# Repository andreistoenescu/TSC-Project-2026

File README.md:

# Watch_TSC_Project

Un smartwatch construit de la zero — schematic, PCB 4 straturi, carcasă 3D — centrat pe nRF52840 și un display E-Paper care nu consumă energie când nu se schimbă nimic pe ecran.

---

## Ce este acest proiect

Scopul a fost să proiectez un ceas inteligent complet: de la primul simbol în schematic până la modelul 3D gata de imprimat. Nu un modul dev board montat într-o carcasă, ci un PCB custom cu toate componentele alese și integrate manual.

Tehnologia cheie este display-ul **E-Paper (e-ink)** — odată ce afișează ceva, menține imaginea fără niciun consum de curent. Combinat cu modurile deep sleep ale nRF52840 (1.5μA), rezultatul este un dispozitiv care poate rula zile întregi dintr-o celulă LiPo mică.

### Ce integrează placa

| Subsistem | Componentă | Rol |
|-----------|-----------|-----|
| Microcontroller | nRF52840 | Cortex-M4 64MHz, BT 5.0, USB nativ |
| Display | E-Paper via SPI | Afișaj zero-consum în standby |
| Mișcare | BMA423 | Accelerometru 3 axe, step counter, wake-on-wrist |
| Încărcare | BQ25180 | LiPo charger programabil I2C, 5mA–1A |
| Alimentare | RT6160 | Buck-Boost 3.3V stabil indiferent de tensiunea bateriei |
| Baterie | MAX17048 | Fuel gauge ModelGauge, fără shunt rezistor |
| Feedback | DRV2605 | Driver haptic, 123 efecte ERM/LRA |
| USB | KH-TYPE-C-16P + USBLC6 | Conector C16P cu protecție ESD ±15kV |
| Input | EVP-AKE31A ×3 | Butoane tactile SMD ultra-subțiri |
| RF | 2450AT18B100E | Antenă SMD 2.45GHz pentru Bluetooth |

---

## Diagrama bloc a sistemului

```
  USB-C (5V)
      │
      ▼
 ┌─────────┐    VBUS      ┌──────────────┐
 │  ESD    │─────────────▶│  BQ25180     │ LiPo Charger
 │USBLC6   │              │  (I2C 0x6A)  │◀─── Baterie LiPo
 └────┬────┘              └──────┬───────┘
      │ D+/D−                    │ VBAT
      │                          ▼
      │                   ┌──────────────┐
      │                   │  MAX17048    │ Fuel Gauge
      │                   │  (I2C 0x36)  │
      │                   └──────┬───────┘
      │                          │ VBAT
      │                          ▼
      │                   ┌──────────────┐
      │                   │   RT6160     │ Buck-Boost DC/DC
      │                   │  (I2C 0x62)  │─── 3V3 ───────────┐
      │                   └──────────────┘                    │
      │                                                       │
      └───────────────────────────────────────────────────────▼
                                                     ┌─────────────────┐
                    ┌── SPI ──▶ E-Paper Display       │                 │
                    │                                 │   nRF52840      │
                    ├── I2C ──▶ BMA423  (0x18)        │   Cortex-M4     │
                    │       ──▶ DRV2605 (0x5A)        │   64MHz / BT5.0 │
                    │       ──▶ BQ25180 (0x6A)        │                 │
                    │       ──▶ RT6160  (0x62)        └────────┬────────┘
                    │       ──▶ MAX17048(0x36)                 │
                    │                                          │ GPIO
                    ├── SWD ──▶ TC2030-IDC                     │
                    │                                          ▼
                    └── USB ──▶ (intern nRF52840)      Butoane ×3 / IMU INT / HAPTIC_EN
```

---

## Componente — BOM complet

| Ref | Part Number | Descriere | Qty |
|-----|------------|-----------|:---:|
| U1 | nRF52840-QIAA | MCU ARM Cortex-M4, BT 5.0, USB 2.0, 1MB Flash | 1 |
| IC1 | BQ25180YBGR | LiPo charger liniar 1A I2C, 8-DSBGA | 1 |
| IC2 | DRV2605YZFR | Haptic driver ERM/LRA I2C 123 efecte, 9-BGA | 1 |
| IC3 | BMA423 | Accelerometru MEMS triaxial 12-bit, LGA-12 | 1 |
| U3 | MAX17048G+T10 | Fuel gauge ModelGauge 1-cell, SOT-23-6 | 1 |
| IC9 | RT6160AWSC | Buck-Boost DC/DC 800mA I2C, 15-WL-CSP | 1 |
| D3 | USBLC6-2SC6Y | TVS ESD ±15kV bidirecțional USB, SOT-23-6 | 1 |
| J4 | KH-TYPE-C-16P | Conector USB-C 16 pini SMD | 1 |
| J1 | 503480-2400 | Conector FPC/FFC 0.5mm pas 24 circuite | 1 |
| J2 | TC2030-IDC | Tag-Connect SWD 6 pini footprint-only | 1 |
| Q2 | DMG2305UX-7 | P-MOSFET 20V/4.2A, SOT-23 | 1 |
| Q3 | SI1308EDL-T1-GE3 | N-MOSFET 30V/1.5A, SC-70 | 1 |
| D1,D2,D5 | MBR0530 | Schottky 30V/500mA, SOD-123 | 3 |
| SW_* | EVP-AKE31A | Buton tactil SMD ultra-subțire Panasonic | 3 |
| ANT1 | 2450AT18B100E | Antenă SMD 2.45GHz Johanson | 1 |
| L7 | FTC252012SR47MBCA | Inductor 0.47μH SMD 2016 | 1 |
| L5 | 744043680 | Inductor 68μH WE-TPC SMD | 1 |
| X1 | Crystal 32MHz | Oscilator SMD 32MHz 2016 | 1 |
| X2 | Crystal 32.768kHz | Oscilator RTC 32.768kHz 3215 SMD | 1 |
| Cx | — | Condensatoare SMD 0201/0402, 1pF–22μF | ~50 |
| Rx | — | Rezistoare SMD 0201, 2.2Ω–10kΩ | ~15 |
| Lx | — | Inductoare SMD 0402, 3.9nH–10μH | ~4 |
| TP_* | TP20R | Test pad SMD 2mm | 14 |
| SJ1 | — | Solder jumper SMD | 1 |

---

## Hardware în detaliu

### Cum circulă energia

Bateria LiPo (3.7–4.2V) alimentează regulatorul **RT6160** care produce un 3V3 stabil pentru toată placa. Când e conectat USB-C, VBUS (5V) merge direct la **BQ25180** care preia încărcarea bateriei independent de restul sistemului. nRF52840 monitorizează ambele stări: știe când USB e prezent (CHARGER_PG) și câtă baterie a mai rămas (MAX17048 via I2C).

Componentele cu consum ridicat — display-ul și haptic driver-ul — sunt controlate prin MOSFET-uri (Q2/Q3), astfel că nRF52840 le poate tăia complet alimentarea când nu sunt necesare.

### Magistrala I2C — 5 periferice pe aceleași fire

| Componentă | Adresă I2C | Ce face |
|------------|:----------:|---------|
| BQ25180 | 0x6A | Controlează curentul și tensiunea de încărcare |
| RT6160 | 0x62 | Ajustează tensiunea de ieșire dacă e necesar |
| BMA423 | 0x18 | Livrează date accelerometru, numără pași |
| MAX17048 | 0x36 | Raportează SOC% și tensiunea celulei |
| DRV2605 | 0x5A | Selectează și redă efecte tactile |

Clock pe **P0.06**, date pe **P0.07**. Rezistoare de pull-up pe ambele linii.

### SPI — display E-Paper

Comunicație write-only spre display (nu există linie MISO — displayul nu trimite date înapoi). Frecvență maximă 4MHz. Pe lângă SCK și MOSI, display-ul are nevoie de 3 semnale GPIO suplimentare: DC (Data/Command), RST (reset hardware) și BUSY (ceasul trebuie să aștepte când displayul procesează un refresh).

### SWD — programare și debug

Conectorul **TC2030-IDC** (Tag-Connect, fără pini fizici pe PCB) expune SWDIO, SWDCLK, SWO și RESET. Nu ocupă spațiu vertical în ansamblu — cablul de programare se atașează temporar prin spring pins direct pe pad-urile de pe PCB.

### Bluetooth și antena

Antena **2450AT18B100E** este o antenă SMD ceramică pentru 2.4GHz, plasată în colțul plăcii cu un cutout în substrat sub ea. Cutout-ul elimină FR4-ul (material dielelectric cu pierderi la 2.4GHz) din zona de radiație, îmbunătățind câștigul și SWR-ul antenei. Cristalul de 32MHz asigură referința de frecvență pentru radio.

### Cristalul de 32.768kHz — RTC în sleep

Al doilea oscilator, la 32.768kHz, alimentează timer-ul RTC al nRF52840 și rămâne activ chiar și în deep sleep. Permite ceasului să știe ora exactă și să se trezească la intervale precise fără să țină procesorul pornit.

### BMA423 — mai mult decât un accelerometru

BMA423 are un procesor intern dedicat care rulează algoritmii de step counting și wake-on-wrist fără să implice nRF52840. Când detectează mișcarea caracteristică ridicării mâinii, trimite o întrerupere pe **P1.08 (IMU_INT1)** care trezește MCU-ul din deep sleep în microsecunde. Consum în această stare: **0.9μA**.

### Estimare consum și autonomie

| Scenariu | Curent estimat |
|----------|:-------------:|
| nRF52840 TX Bluetooth activ | 6.26 mA |
| nRF52840 RX Bluetooth activ | 4.82 mA |
| Refresh display E-Paper | ~26 mA (câteva secunde) |
| BMA423 monitorizare continuă | 130 μA |
| MAX17048 fuel gauge activ | 23 μA |
| DRV2605 vibrație activă | 5 mA |
| nRF52840 deep sleep + RTC + BMA low-power | ~50–100 μA |

**Consum mediu în utilizare normală** (BT conectat periodic, display refresh la fiecare minut, IMU activ): **6–8 mA** la 3.3V.

Cu o baterie LiPo de **300mAh**: autonomie estimată **35–50 ore**.

---

## Alocarea pinilor nRF52840

### Display E-Paper (SPI)

| Pin MCU | Semnal | Direcție | Descriere |
|---------|--------|:--------:|-----------|
| P0.02 / AIN0 | SCK | OUT | Clock SPI pentru display |
| P0.03 / AIN1 | MOSI | OUT | Date seriale spre display |
| P0.05 / AIN3 | EPD_CS | OUT | Chip select, activ LOW |
| P0.15 | EPD_RST | OUT | Reset hardware display, activ LOW |
| P0.16 | EPD_DC | OUT | LOW = comandă, HIGH = date |
| P0.17 | EPD_BUSY | IN | HIGH când displayul procesează |

### Periferice I2C

| Pin MCU | Semnal | Descriere |
|---------|--------|-----------|
| P0.06 | SCL | Clock comun pentru toate perifericele I2C |
| P0.07 | SDA | Date bidirecționale I2C |
| P0.08 | IMU_INT2 | Întrerupere secundară BMA423 (step counter) |
| P1.08 | IMU_INT1 | Întrerupere primară BMA423 (wake-on-wrist) |
| P0.10 / NFC2 | FUELGAUGE_ALT | Alarmă MAX17048 la baterie scăzută |
| P0.11 | CHARGER_PG | Power Good BQ25180 — 1 când USB e valid |
| P0.12 | HAPTIC_EN | Enable DRV2605, activ HIGH |

### Butoane și control

| Pin MCU | Semnal | Descriere |
|---------|--------|-----------|
| P0.13 | BTN_UP | Buton sus (navigare meniu) |
| P0.14 | BTN_ENT | Buton enter / confirmare |
| P1.02 | BTN_DN | Buton jos (navigare meniu) |

### USB, SWD și ceasuri

| Pin MCU | Semnal | Interfață | Descriere |
|---------|--------|:---------:|-----------|
| D+ | USB_DP | USB | Linie diferențială pozitivă, prin ESD |
| D− | USB_DM | USB | Linie diferențială negativă, prin ESD |
| VBUS | 5V_USB | PWR | Detecție USB prezent → BQ25180 |
| SWDIO | SWDIO | SWD | Date programare/debug |
| SWDCLK | SWDCLK | SWD | Clock programare/debug |
| SWO | SWO | SWD | Serial Wire Output (trace) |
| P0.18 / RESET | RESET | GPIO | Reset hardware MCU |
| ANT | RF | RF | Antenă Bluetooth 2.4GHz |
| XC1, XC2 | XTAL_32M | CLK | Cristal 32MHz — clock principal |
| XL1, XL2 | XTAL_32K | CLK | Cristal 32.768kHz — RTC sleep |

---

## PCB — decizii de proiectare

### 4 straturi: de ce și cum

| Strat | Conținut |
|-------|---------|
| **L1 — Top** | Toate componentele SMD + rutare semnale principale |
| **L2** | Plan de masă GND continuu |
| **L3** | Plan de alimentare 3V3 |
| **L4 — Bottom** | Rutare secundară + via connections |

Planul de masă pe L2 direct sub stratul de semnal L1 minimizează inductanța buclei de return pentru fiecare traseu. Fără acest plan, semnalele SPI și I2C ar genera mai mult EMI și ar fi mai sensibile la zgomot. Planul de 3V3 pe L3 reduce impedanța de alimentare, esențial pentru vârfurile de curent ale nRF52840 în TX.

### Via-in-pad

BQ25180, RT6160, DRV2605 și MAX17048 vin în packaging BGA/CSP cu pitch sub 0.5mm — imposibil de rutat cu via-uri laterale în spațiul disponibil. Soluția: via-uri plasate direct în centrul pad-urilor BGA. Acestea trebuie **umplute cu rășină epoxidică și planarize** (filled & capped) înainte de HASL/ENIG, altfel pasta de lipit curge în via și jointul devine defectuos.

### Cutout sub antenă

Substatul FR4 este un material cu pierderi dielectrice la 2.4GHz. Lăsat sub zona de radiație a antenei 2450AT18B100E, absoarbe o parte din energia RF și detune antena față de 50Ω. Soluția: un decupaj fizic al PCB-ului sub jumătatea neconectată a antenei, astfel că aceasta radiază în aer.

### 14 test pad-uri TP20R

Distribuite pe semnalele: 3V3, VBAT, GND, SDA, SCL, SWDCLK, SWDIO, SWO, RESET, VREG. Permit conectarea unui multimetru sau logicanalyzer după asamblare fără a fi nevoie de probe pe QFN/BGA.

---

## Ansamblu 3D

Modelat complet în **Autodesk Fusion 360**. Ansamblul verifică că totul se potrivește fizic înainte de fabricație.

Stratificarea de jos în sus:

```
  ┌─────────────────────────┐  ← Cadru superior + geam display
  │     Display E-Paper     │  ← Panou e-ink + cablu FPC
  │         PCB             │  ← Placa cu toate componentele
  │      Baterie LiPo       │  ← Celulă cu fire sudate pe test pads
  └─────────────────────────┘  ← Carcasă inferioară
```

Butoanele (×3) sunt accesibile prin locașuri în carcasa inferioară, pe laterale. Conectorul USB-C iese prin fanta frontală a carcasei. Shaker-ul haptic este montat cilindric în spațiul rămas lângă baterie.

---

## Galerie

### PCB — Layout 2D

### PCB — Randare 3D

### Ceas asamblat

### Exploded View

### Baterie LiPo

### Display E-Paper

### Motor Haptic

---

## Structura repository-ului

```
Watch_TSC_Project/
│
├── Hardware/
│   ├── PCB_2D.brd              # Fișier board KiCad/Eagle
│   ├── Schematic_final.sch     # Schematic complet
│   └── Schematic_final.pdf     # Export PDF schematic
│
├── Manufacturing/
│   ├── gerbers.zip             # Fișiere Gerber pentru fabricație PCB
│   ├── Watch_TSC_bom.bom       # Bill of Materials pentru comandă componente
│   ├── PnP_Watch_TSC_front.cpl # Pick & Place față
│   └── PnP_Watch_TSC_back.cpl  # Pick & Place spate
│
├── Mechanical/
│   ├── Exploded_Watch_3D.zip   # Export STEP ansamblu exploded
│   └── Watch_3D.f3z            # Proiect Autodesk Fusion 360
│
├── Images/                     # Randări și capturi PCB
│
├── LICENSE
└── README.md
```

---

MIT License — Copyright 2026 Stoenescu Constantin-Andrei

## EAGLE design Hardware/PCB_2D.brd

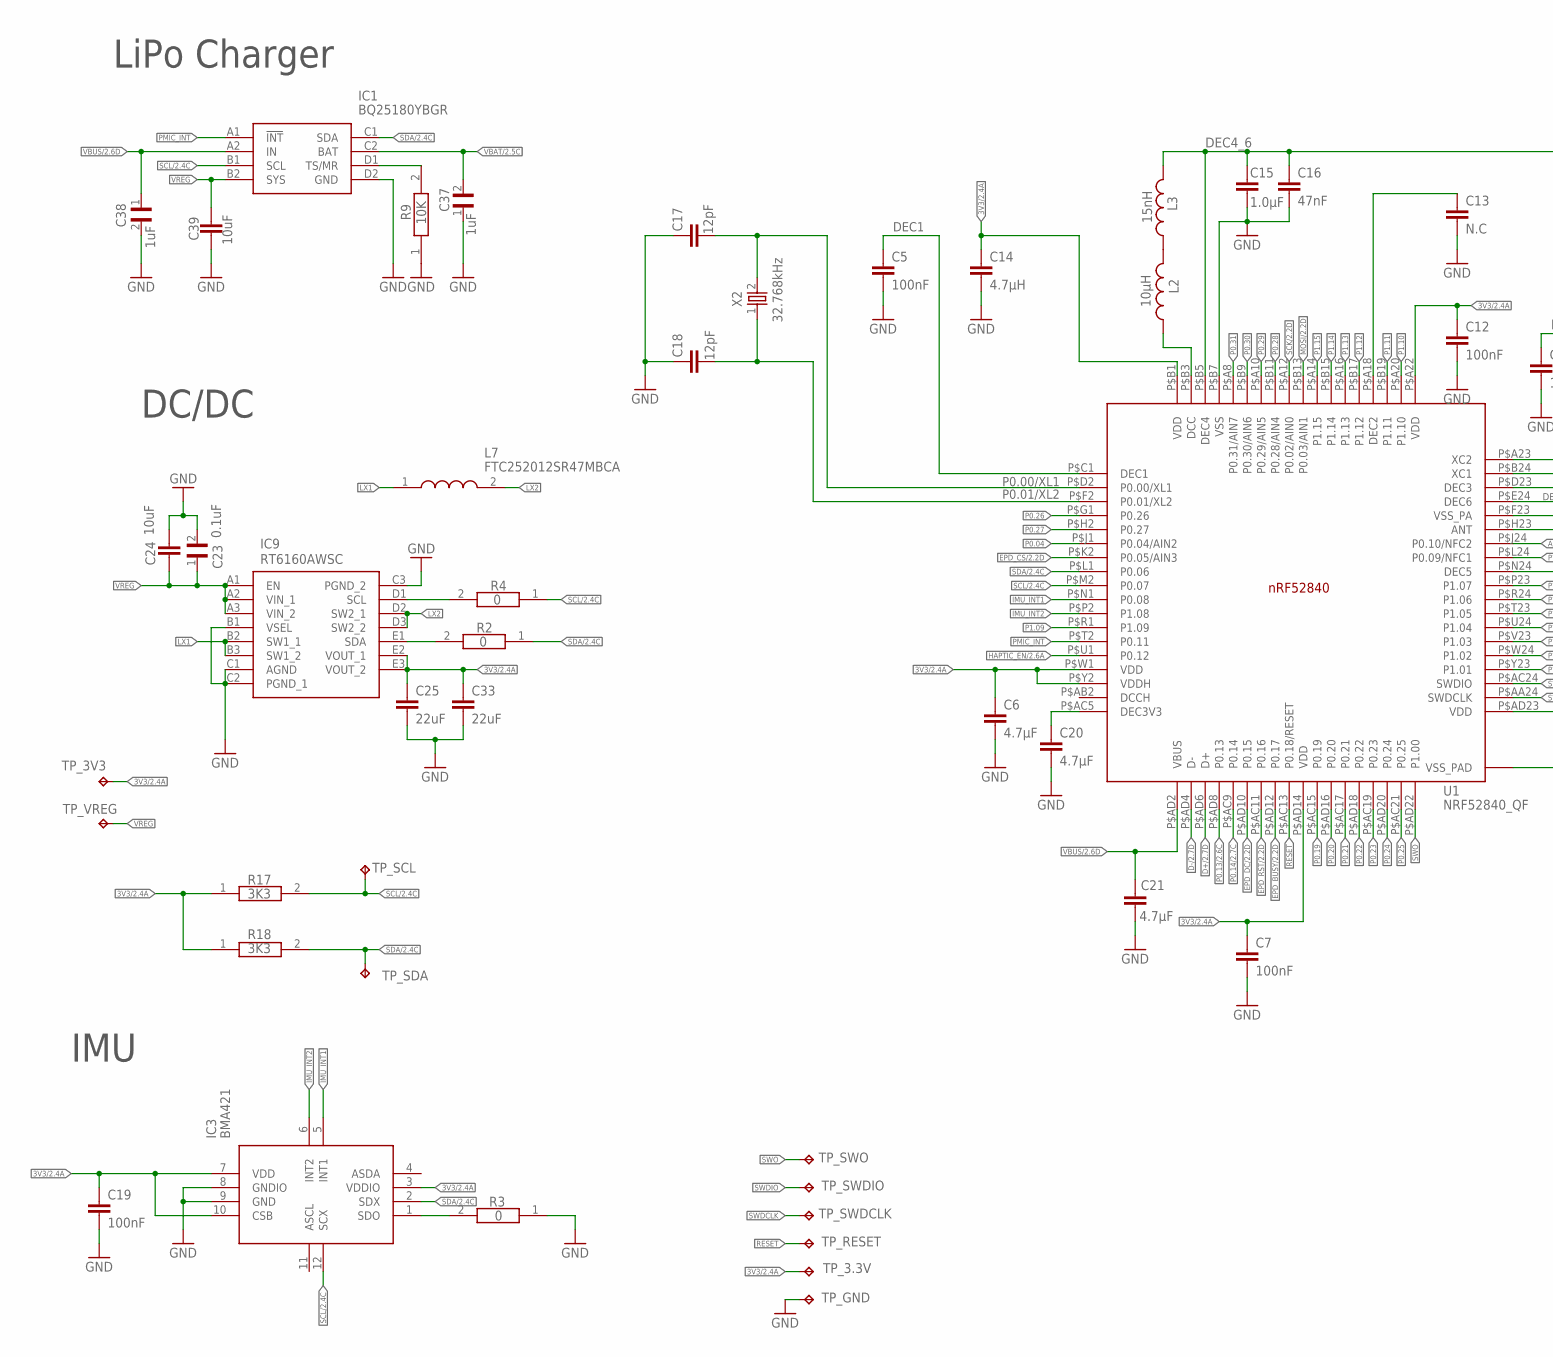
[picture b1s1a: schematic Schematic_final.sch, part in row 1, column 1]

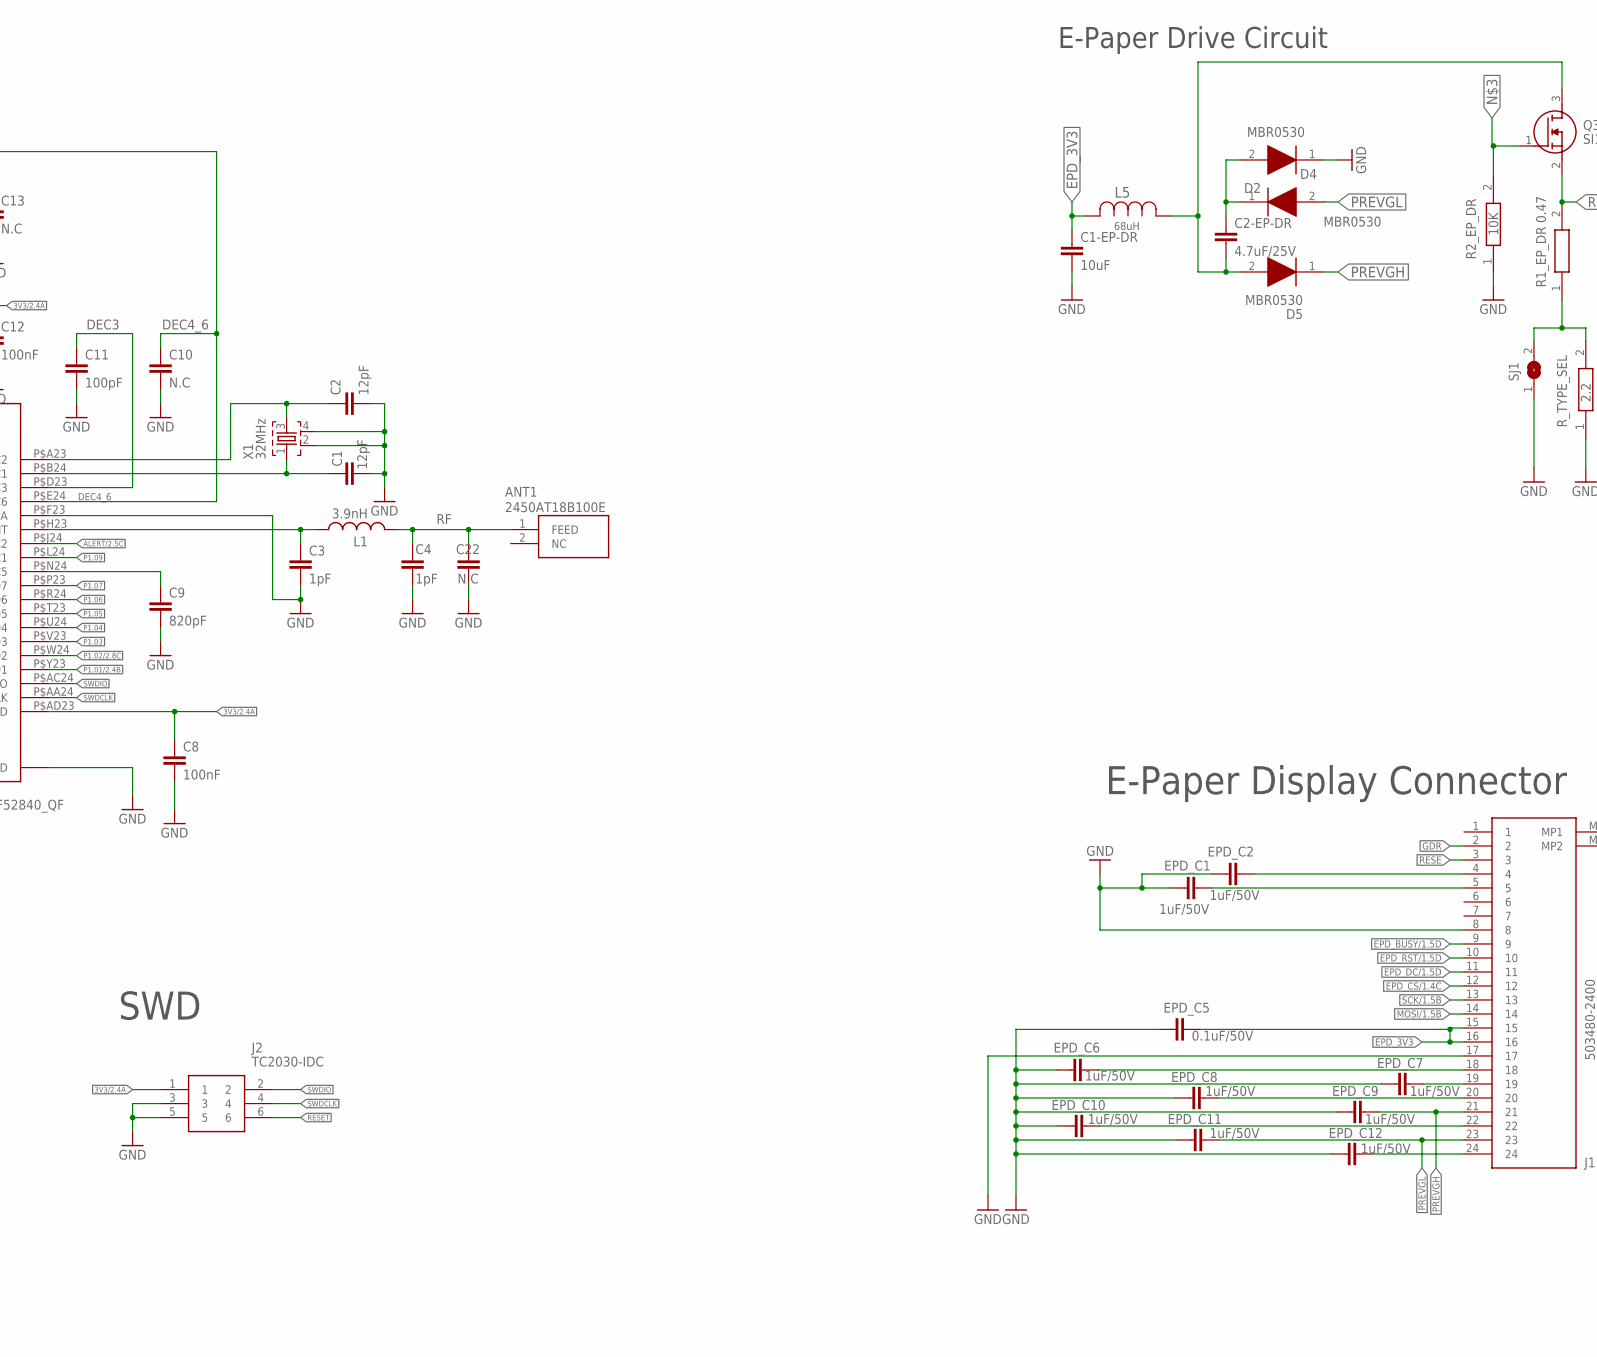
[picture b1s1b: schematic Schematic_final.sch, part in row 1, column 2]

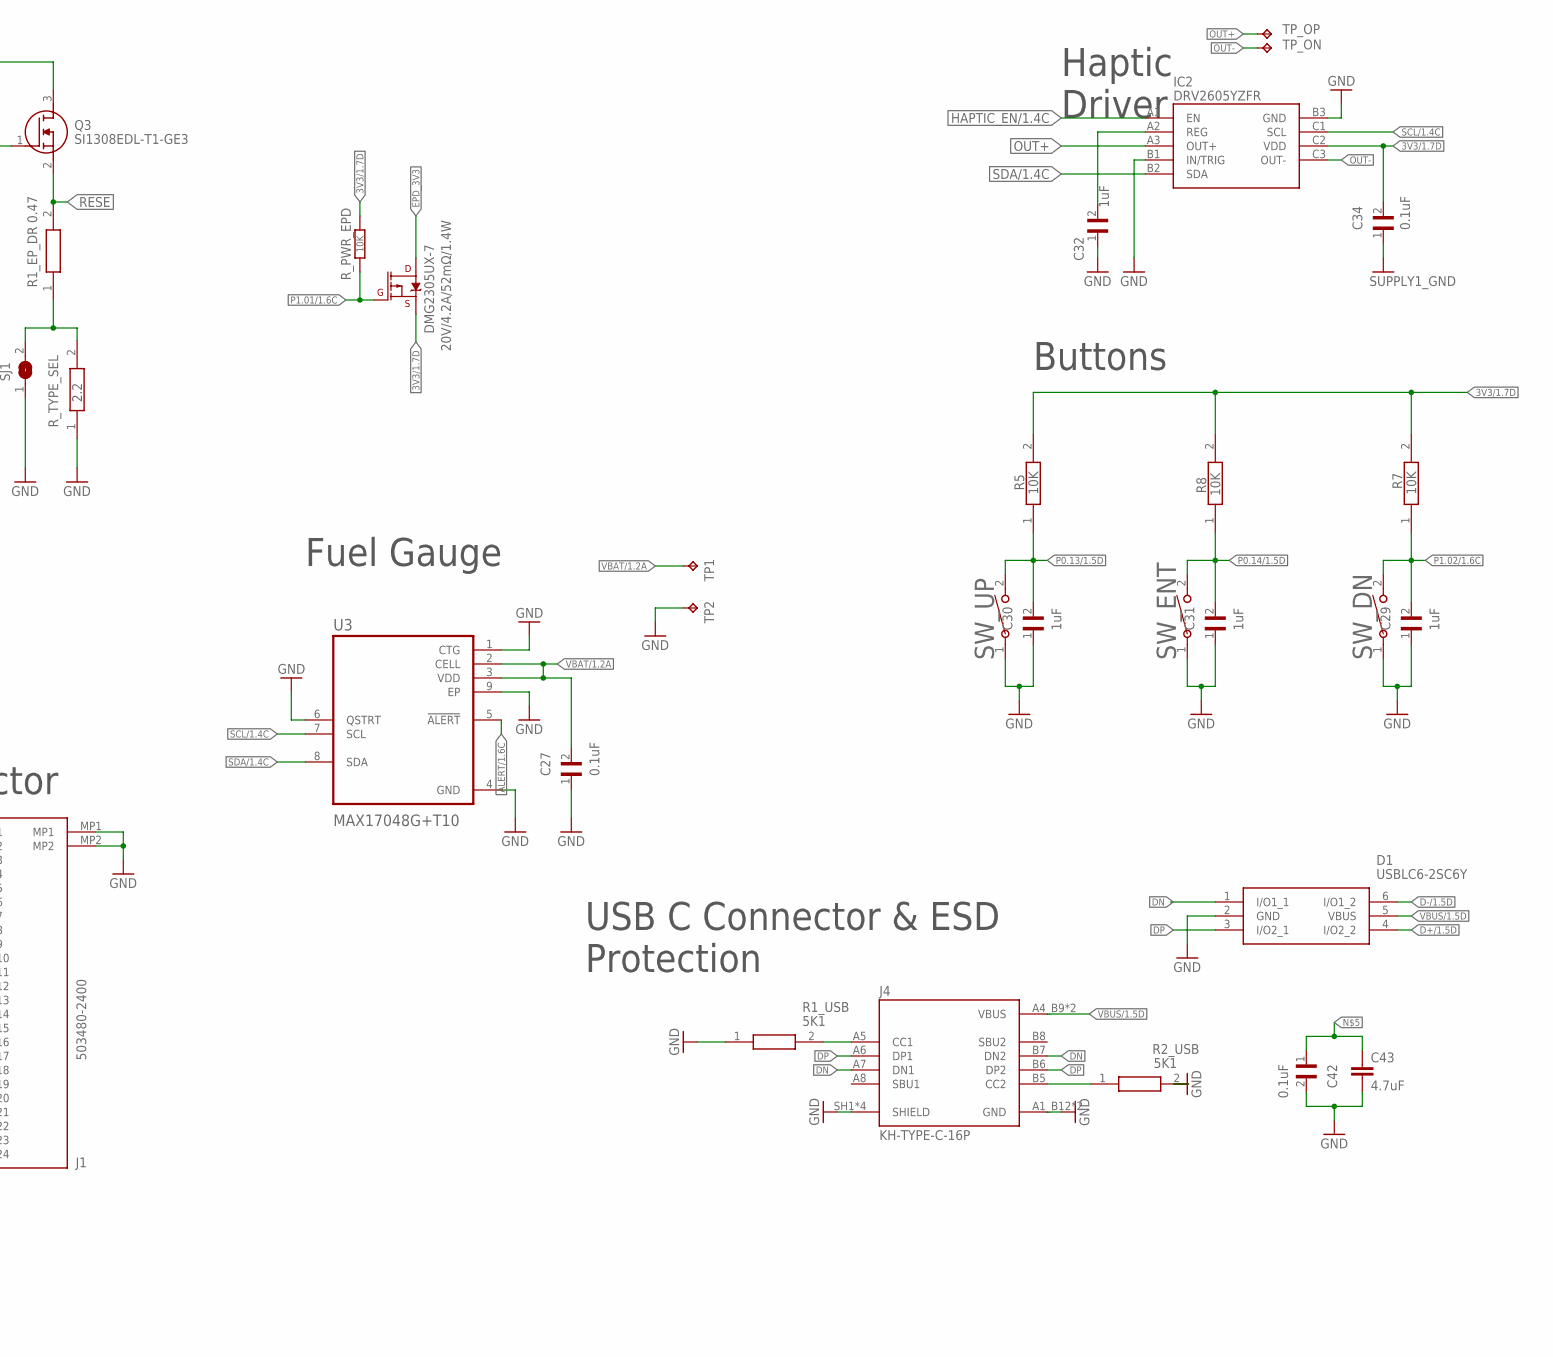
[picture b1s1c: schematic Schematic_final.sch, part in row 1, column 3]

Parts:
ANT1: 2450AT18B100E; 2450AT18B100E_ANTC3216X140N
C1, C2, C17, C18: 12pF; NORDIC_NRF_3_RESC0201_L
C1-EP-DR, C24, C39: 10uF; NORDIC_NRF_3_RESC0201_L
C2-EP-DR: 4.7uF/25V; NORDIC_NRF_3_RESC0201_L
C3, C4: 1pF; NORDIC_NRF_3_RESC0201_L
C5, C7, C8, C12, C19: 100nF; NORDIC_NRF_3_RESC0201_L
C6, C20, C21: 4.7μF; NORDIC_NRF_3_RESC0201_L
C9: 820pF; NORDIC_NRF_3_RESC0201_L
C10, C13, C22: N.C; NORDIC_NRF_3_RESC0201_L
C11: 100pF; NORDIC_NRF_3_RESC0201_L
C14: 4.7μH; NORDIC_NRF_3_RESC0201_L
C15: 1.0μF; NORDIC_NRF_3_RESC0201_L
C16: 47nF; NORDIC_NRF_3_RESC0201_L
C23, C27, C34, C42: 0.1uF; GRM011R60J152KE01L_2_CAPC0201X13N
C25, C33: 22uF; NORDIC_NRF_3_RESC0201_L
C29, C30, C31, C32, C37, C38: 1uF; GRM011R60J152KE01L_2_CAPC0201X13N
C43: 4.7uF; NORDIC_NRF_3_RESC0201_L
D1: USBLC6-2SC6Y; ESP32_C6_LIBRARY_3_SOT95P280X145-6N
D2, D4, D5: MBR0530; ESP32_C6_LIBRARY_5_SOD3716X135N
DMG2305UX-7: 20V/4.2A/52mΩ/1.4W; ESP32_C6_LIBRARY_4_ESP32_C6_LIBRARY_4_ESP32_C6_LIBRARY_4_ES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
EPD_C1, EPD_C2, EPD_C6, EPD_C7, EPD_C8, EPD_C9, EPD_C10, EPD_C11, EPD_C12: 1uF/50V; NORDIC_NRF_3_RESC0201_L
EPD_C5: 0.1uF/50V; NORDIC_NRF_3_RESC0201_L
IC1: BQ25180YBGR; BQ25180YBGR_BGA8C40P2X4_100X155X50
IC2: DRV2605YZFR; DRV2605YZFR_BGA9C50P3X3_144X144X62
IC3: BMA421; BMA423_BMA423
IC9: RT6160AWSC; RT6160AWSC_BGA15C40P3X5_140X230X60
J1: 503480-2400; 503480-2400_5034802400
J2: TC2030-IDC; TC2030-IDC_TC2030IDC
J4: KH-TYPE-C-16P; KH-TYPE-C-16P_KINGHELM_KH-TYPE-C-16P
L1: 3.9nH; NORDIC_NRF_2_RESC0402_L
L2: 10μH; NORDIC_NRF_2_RESC0402_L
L3: 15nH; NORDIC_NRF_2_RESC0402_L
L5: 68uH; ESP32_C6_LIBRARY_2_IND_4828-WE-TPC_WRE
L7: FTC252012SR47MBCA; MLP2016SR47MT0S1_INDC2016X100N
Q3: SI1308EDL-T1-GE3; ESP32_C6_LIBRARY_6_SOT65P210X110-3N
R1_EP_DR: 0.47; CPF0201D7K68C1_0201
R1_USB, R2_USB: 5K1; CPF0201D7K68C1_0201
R2, R3, R4: 0; CPF0201D7K68C1_0201
R2_EP_DR, R5, R7, R8, R9: 10K; CPF0201D7K68C1_0201
R17, R18: 3K3; CPF0201D7K68C1_0201
R_PWR_EPD: 10K; RESC1005X40
R_TYPE_SEL: 2.2; CPF0201D7K68C1_0201
SJ1: ESP32_C6_LIBRARY_7_JUMPER_SJ
SW_DN: 2025-10-22_07-23-44_LIBRARY_EVP-AKE31ASW_EVP-AKE3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; 2025-10-22_07-23-44_LIBRARY_SW_EVP-AKE31A_PAN
SW_ENT: 2025-10-22_07-23-44_LIBRARY_EVP-AKE31ASW_EVP-AKE3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; 2025-10-22_07-23-44_LIBRARY_SW_EVP-AKE31A_PAN
SW_UP: 2025-10-22_07-23-44_LIBRARY_EVP-AKE31ASW_EVP-AKE3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; 2025-10-22_07-23-44_LIBRARY_SW_EVP-AKE31A_PAN
TP1, TP2: HECTOR_WATCH_1_TPTP20R; HECTOR_WATCH_1_TP20R
TP_3.3V, TP_3V3: HECTOR_WATCH_1_TPTP20R; HECTOR_WATCH_1_TP20R
TP_GND: HECTOR_WATCH_1_TPTP20R; HECTOR_WATCH_1_TP20R
TP_ON: HECTOR_WATCH_1_TPTP20R; HECTOR_WATCH_1_TP20R
TP_OP: TP_OP; HECTOR_WATCH_1_TP20R
TP_RESET: HECTOR_WATCH_1_TPTP20R; HECTOR_WATCH_1_TP20R
TP_SCL: HECTOR_WATCH_1_TPTP20R; HECTOR_WATCH_1_TP20R
TP_SDA: HECTOR_WATCH_1_TPTP20R; HECTOR_WATCH_1_TP20R
TP_SWDCLK: HECTOR_WATCH_1_TPTP20R; HECTOR_WATCH_1_TP20R
TP_SWDIO: HECTOR_WATCH_1_TPTP20R; HECTOR_WATCH_1_TP20R
TP_SWO: HECTOR_WATCH_1_TPTP20R; HECTOR_WATCH_1_TP20R
TP_VREG: HECTOR_WATCH_1_TPTP20R; HECTOR_WATCH_1_TP20R
U1: NRF52840_QF; NORDIC_NRF_4_AQFN50P700X700X85_HS-74N
U3: MAX17048G+T10; ESP32_C6_LIBRARY_SON50P200X200X80-9N
X1: 32MHz; NORDIC_NRF_BT-XTAL_2016_N
X2: 32.768kHz; NORDIC_NRF_1_XTAL_3215_N

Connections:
3V3/1.7D: C34.2, DMG2305UX-7.2 (S), IC2.C2 (VDD), R5.2, R7.2, R8.2, R_PWR_EPD.2
3V3/2.4A: C6.1, C7.1, C8.1, C12.1, C14.1, C19.1, C25.1, C33.1, IC3.3 (VDDIO), IC3.7 (VDD), IC3.10 (CSB), IC9.E2 (VOUT_1), IC9.E3 (VOUT_2), J2.1, R17.1, R18.1, TP_3.3V.TP, TP_3V3.TP, U1.P$A22 (VDD), U1.P$AD14 (VDD), U1.P$AD23 (VDD), U1.P$B1 (VDD), U1.P$W1 (VDD), U1.P$Y2 (VDDH)
ALERT/1.6C: U3.5 (!ALERT)
ALERT/2.5C: U1.P$J24 (P0.10/NFC2)
D+/1.5D: D1.4 (I/O2_2)
D+/2.7D: U1.P$AD6 (D+)
D-/1.5D: D1.6 (I/O1_2)
D-/2.7D: U1.P$AD4 (D-)
DEC1: C5.1, U1.P$C1 (DEC1)
DEC3: C11.1, U1.P$D23 (DEC3)
DEC4_6: C10.1, C15.1, C16.1, L3.2, U1.P$B5 (DEC4), U1.P$E24 (DEC6)
DN: D1.1 (I/O1_1), J4.A7 (DN1), J4.B7 (DN2)
DP: D1.3 (I/O2_1), J4.A6 (DP1), J4.B6 (DP2)
EPD_3V3: C1-EP-DR.1, DMG2305UX-7.3 (D), EPD_C5.2, J1.15, J1.16, L5.2
EPD_BUSY/1.5D: J1.9
EPD_BUSY/2.2D: U1.P$AD12 (P0.17)
EPD_CS/1.4C: J1.12
EPD_CS/2.2D: U1.P$K2 (P0.05/AIN3)
EPD_DC/1.5D: J1.11
EPD_DC/2.2D: U1.P$AD10 (P0.15)
EPD_RST/1.5D: J1.10
EPD_RST/2.2D: U1.P$AC11 (P0.16)
GDR: J1.2
GND: C1.2, C1-EP-DR.2, C2.2, C3.2, C4.2, C5.2, C6.2, C7.2, C8.2, C9.2, C10.2, C11.2, C12.2, C13.2, C14.2, C15.2, C16.2, C17.1, C18.1, C19.2, C20.2, C21.2, C22.2, C23.2, C24.1, C25.2, C27.1, C29.1, C30.1, C31.1, C32.1, C33.2, C34.1, C37.1, C38.2, C39.2, C42.2, C43.2, D1.2 (GND), D4.1 (K), EPD_C1.1, EPD_C2.1, EPD_C5.1, EPD_C6.1, EPD_C7.1, EPD_C8.1, EPD_C9.1, EPD_C10.1, EPD_C11.1, EPD_C12.1, IC1.D2 (GND), IC2.B1 (IN/TRIG), IC2.B3 (GND), IC3.8 (GNDIO), IC3.9 (GND), IC9.B1 (VSEL), IC9.C1 (AGND), IC9.C2 (PGND_1), IC9.C3 (PGND_2), J1.8, J1.17, J1.MP1, J1.MP2, J2.3, J2.5, J4.A1_B12 (GND), J4.A12_B1 (GND), J4.SH1 (SHIELD), J4.SH2 (SHIELD), J4.SH3 (SHIELD), J4.SH4 (SHIELD), R1_USB.1, R2_EP_DR.1, R2_USB.2, R3.1, R9.1, R_TYPE_SEL.1, SJ1.1, SW_DN.1, SW_ENT.1, SW_UP.1, TP2.TP, TP_GND.TP, U1.P$74 (VSS_PAD), U1.P$75 (VSS_PAD), U1.P$76 (VSS_PAD), U1.P$77 (VSS_PAD), U1.P$78 (VSS_PAD), U1.P$79 (VSS_PAD), U1.P$80 (VSS_PAD), U1.P$81 (VSS_PAD), U1.P$82 (VSS_PAD), U1.P$83 (VSS_PAD), U1.P$84 (VSS_PAD), U1.P$85 (VSS_PAD), U1.P$86 (VSS_PAD), U1.P$87 (VSS_PAD), U1.P$88 (VSS_PAD), U1.P$89 (VSS_PAD), U1.P$90 (VSS_PAD), U1.P$B7 (VSS), U1.P$F23 (VSS_PA), U3.1 (CTG), U3.4 (GND), U3.6 (QSTRT), U3.9 (EP), X1.2, X1.4
HAPTIC_EN/1.4C: IC2.A1 (EN)
HAPTIC_EN/2.6A: U1.P$U1 (P0.12)
IMU_INT1: IC3.5 (INT1), U1.P$N1 (P0.08)
IMU_INT2: IC3.6 (INT2), U1.P$P2 (P1.08)
LX1: IC9.B2 (SW1_1), IC9.B3 (SW1_2), L7.1
LX2: IC9.D2 (SW2_1), IC9.D3 (SW2_2), L7.2
MOSI/1.5B: J1.14
MOSI/2.2D: U1.P$B13 (P0.03/AIN1)
unnamed: C2-EP-DR.2, D5.2 (A), L5.1, Q3.3 (D)
unnamed: C2-EP-DR.1, D2.1 (K), D4.2 (A)
unnamed: Q3.1 (G), R2_EP_DR.2
unnamed: R1_EP_DR.1, R_TYPE_SEL.2, SJ1.2
unnamed: C42.1, C43.1
unnamed: C32.2, IC2.A2 (REG)
unnamed: IC1.D1 (TS/MR), R9.2
unnamed: J4.A5 (CC1), R1_USB.2
unnamed: IC3.1 (SDO), R3.2
unnamed: EPD_C2.2, J1.4
unnamed: EPD_C1.2, J1.5
unnamed: IC9.D1 (SCL), R4.2
unnamed: IC9.E1 (SDA), R2.2
unnamed: J4.B5 (CC2), R2_USB.1
unnamed: C20.1, U1.P$AC5 (DEC3V3)
unnamed: EPD_C6.2, J1.18
unnamed: EPD_C7.2, J1.19
unnamed: EPD_C8.2, J1.20
unnamed: EPD_C10.2, J1.22
unnamed: EPD_C12.2, J1.24
unnamed: C9.1, U1.P$N24 (DEC5)
unnamed: C3.1, L1.1, U1.P$H23 (ANT)
unnamed: C2.1, U1.P$A23 (XC2), X1.3
unnamed: C1.1, U1.P$B24 (XC1), X1.1
unnamed: C13.1, U1.P$A18 (DEC2)
unnamed: L2.1, U1.P$B3 (DCC)
unnamed: L2.2, L3.1
OUT+: IC2.A3 (OUT+), TP_OP.TP
OUT-: IC2.C3 (OUT-), TP_ON.TP
P0.00/XL1: C17.2, U1.P$D2 (P0.00/XL1), X2.2
P0.01/XL2: C18.2, U1.P$F2 (P0.01/XL2), X2.1
P0.04: U1.P$J1 (P0.04/AIN2)
P0.13/1.5D: C30.2, R5.1, SW_UP.2
P0.13/2.6C: U1.P$AD8 (P0.13)
P0.14/1.5D: C31.2, R8.1, SW_ENT.2
P0.14/2.7C: U1.P$AC9 (P0.14)
P0.19: U1.P$AC15 (P0.19)
P0.20: U1.P$AD16 (P0.20)
P0.21: U1.P$AC17 (P0.21)
P0.22: U1.P$AD18 (P0.22)
P0.23: U1.P$AC19 (P0.23)
P0.24: U1.P$AD20 (P0.24)
P0.25: U1.P$AC21 (P0.25)
P0.26: U1.P$G1 (P0.26)
P0.27: U1.P$H2 (P0.27)
P0.28: U1.P$B11 (P0.28/AIN4)
P0.29: U1.P$A10 (P0.29/AIN5)
P0.30: U1.P$B9 (P0.30/AIN6)
P0.31: U1.P$A8 (P0.31/AIN7)
P1.01/1.6C: DMG2305UX-7.1 (G), R_PWR_EPD.1
P1.01/2.4B: U1.P$Y23 (P1.01)
P1.02/1.6C: C29.2, R7.1, SW_DN.2
P1.02/2.8C: U1.P$W24 (P1.02)
P1.03: U1.P$V23 (P1.03)
P1.04: U1.P$U24 (P1.04)
P1.05: U1.P$T23 (P1.05)
P1.06: U1.P$R24 (P1.06)
P1.07: U1.P$P23 (P1.07)
P1.09: U1.P$L24 (P0.09/NFC1), U1.P$R1 (P1.09)
P1.10: U1.P$A20 (P1.10)
P1.11: U1.P$B19 (P1.11)
P1.12: U1.P$B17 (P1.12)
P1.13: U1.P$A16 (P1.13)
P1.14: U1.P$B15 (P1.14)
P1.15: U1.P$A14 (P1.15)
PMIC_INT: IC1.A1 (!INT), U1.P$T2 (P0.11)
PREVGH: D5.1 (K), EPD_C9.2, J1.21
PREVGL: D2.2 (A), EPD_C11.2, J1.23
RESE: J1.3, Q3.2 (S), R1_EP_DR.2
RESET: J2.6, TP_RESET.TP, U1.P$AC13 (P0.18/RESET)
RF: ANT1.1 (FEED), C4.1, C22.1, L1.2
SCK/1.5B: J1.13
SCK/2.2D: U1.P$A12 (P0.02/AIN0)
SCL/1.4C: IC2.C1 (SCL), U3.7 (SCL)
SCL/2.4C: IC1.B1 (SCL), IC3.12 (SCX), R4.1, R17.2, TP_SCL.TP, U1.P$M2 (P0.07)
SDA/1.4C: IC2.B2 (SDA), U3.8 (SDA)
SDA/2.4C: IC1.C1 (SDA), IC3.2 (SDX), R2.1, R18.2, TP_SDA.TP, U1.P$L1 (P0.06)
SWDCLK: J2.4, TP_SWDCLK.TP, U1.P$AA24 (SWDCLK)
SWDIO: J2.2, TP_SWDIO.TP, U1.P$AC24 (SWDIO)
SWO: TP_SWO.TP, U1.P$AD22 (P1.00)
VBAT/1.2A: C27.2, TP1.TP, U3.2 (CELL), U3.3 (VDD)
VBAT/2.5C: C37.2, IC1.C2 (BAT)
VBUS/1.5D: D1.5 (VBUS), J4.A4_B9 (VBUS), J4.A9_B4 (VBUS)
VBUS/2.6D: C21.1, C38.1, IC1.A2 (IN), U1.P$AD2 (VBUS)
VREG: C23.1, C24.2, C39.1, IC1.B2 (SYS), IC9.A1 (EN), IC9.A2 (VIN_1), IC9.A3 (VIN_2), TP_VREG.TP

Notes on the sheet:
E-Paper Drive Circuit
Fuel Gauge
E-Paper Display Connector
Buttons
Haptic Driver
USB C Connector & ESD Protection
LiPo Charger
DC/DC
IMU
SWD

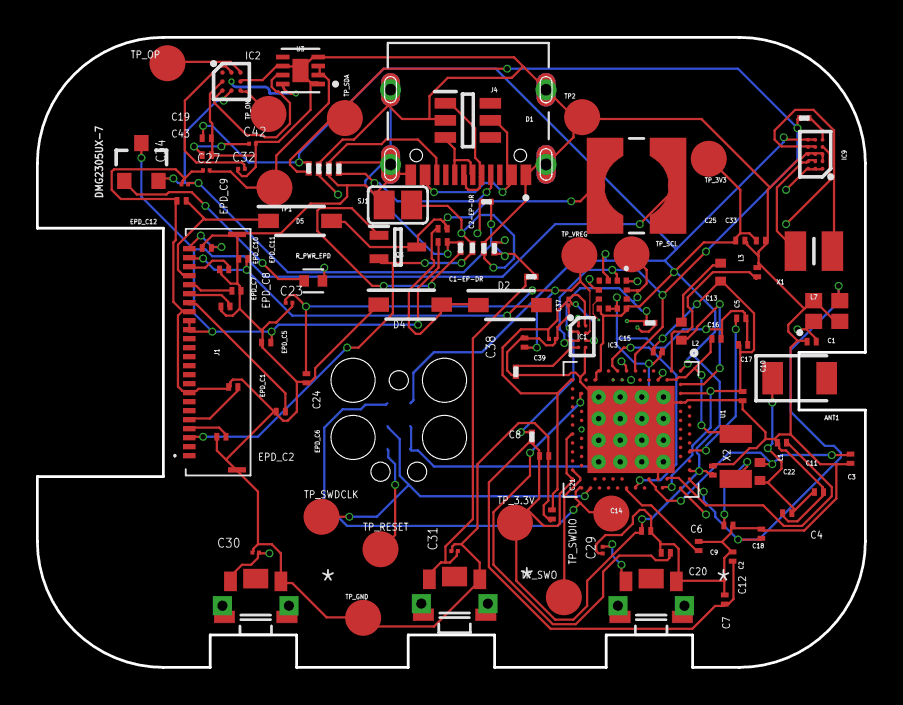
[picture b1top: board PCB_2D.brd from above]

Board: 4 copper layers, 46.0 x 35.0 mm, 105 parts (1 on the bottom side), 67 nets.

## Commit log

2026-04-10 Add project files
2026-04-19 Delete PCB 3d - randare.png
    Clean up non-compliant project files
2026-04-19 Delete PCB3D-Piesa.f3d
    Clean up non-compliant project files
2026-04-19 Delete README.md
    Clean up non-compliant project files
2026-04-19 Delete Schema PCB.brd
    Clean up non-compliant project files
2026-04-19 Delete Schematic.sch
    Clean up non-compliant project files
2026-04-19 Add final project files: hardware, manufacturing, mechanical and images
    Added complete project structure:
    - Hardware: schematics and PCB design files
    - Manufacturing: gerbers, BOM and pick-and-place files
    - Mechanical: 3D assembly files and Fusion360 project
    - Images: final PCB and assembly renders
    - Updated README with full project documentation
2026-04-19 Update README.md
    Fix readme
2026-04-19 Update README.md
    Final version of the README
2026-04-19 Update README.md
    Final final version of the README

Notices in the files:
parts and their libraries:
COPYRIGHT: Copyright (C) 2024 Ultra Librarian. All rights reserved.
COPYRIGHT: Copyright (C) 2025 Ultra Librarian. All rights reserved.
